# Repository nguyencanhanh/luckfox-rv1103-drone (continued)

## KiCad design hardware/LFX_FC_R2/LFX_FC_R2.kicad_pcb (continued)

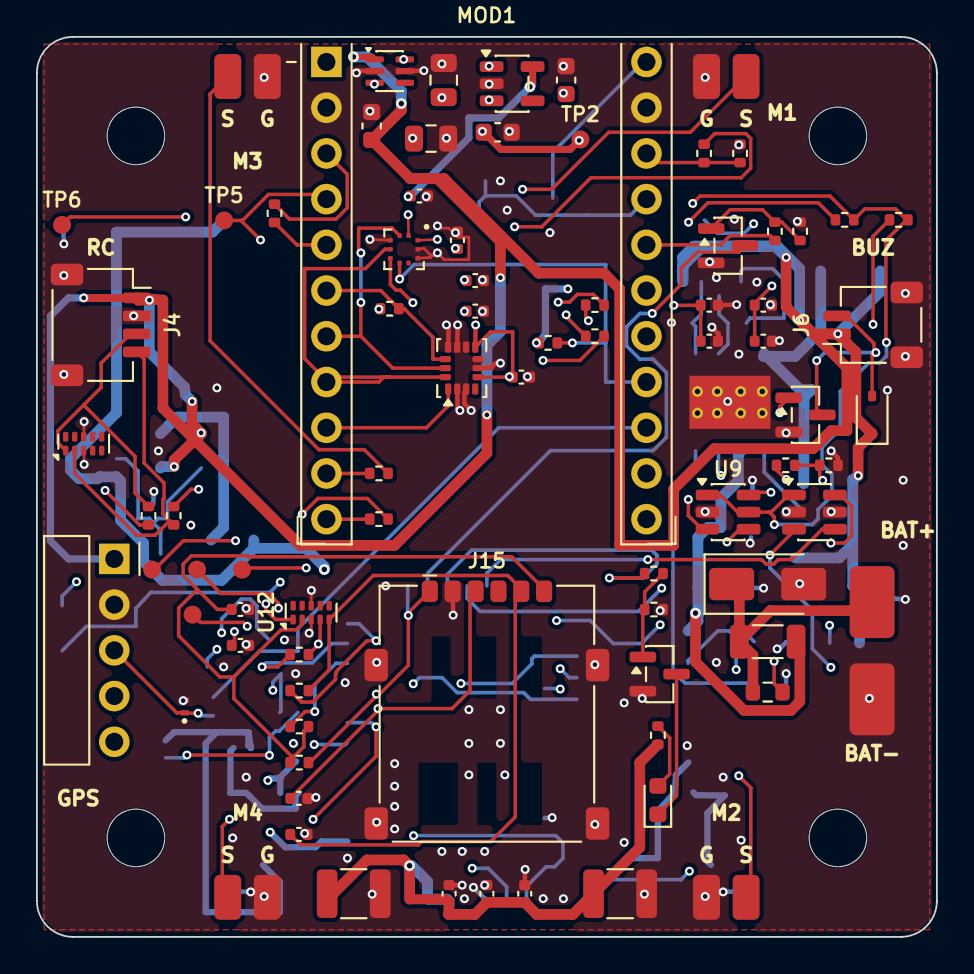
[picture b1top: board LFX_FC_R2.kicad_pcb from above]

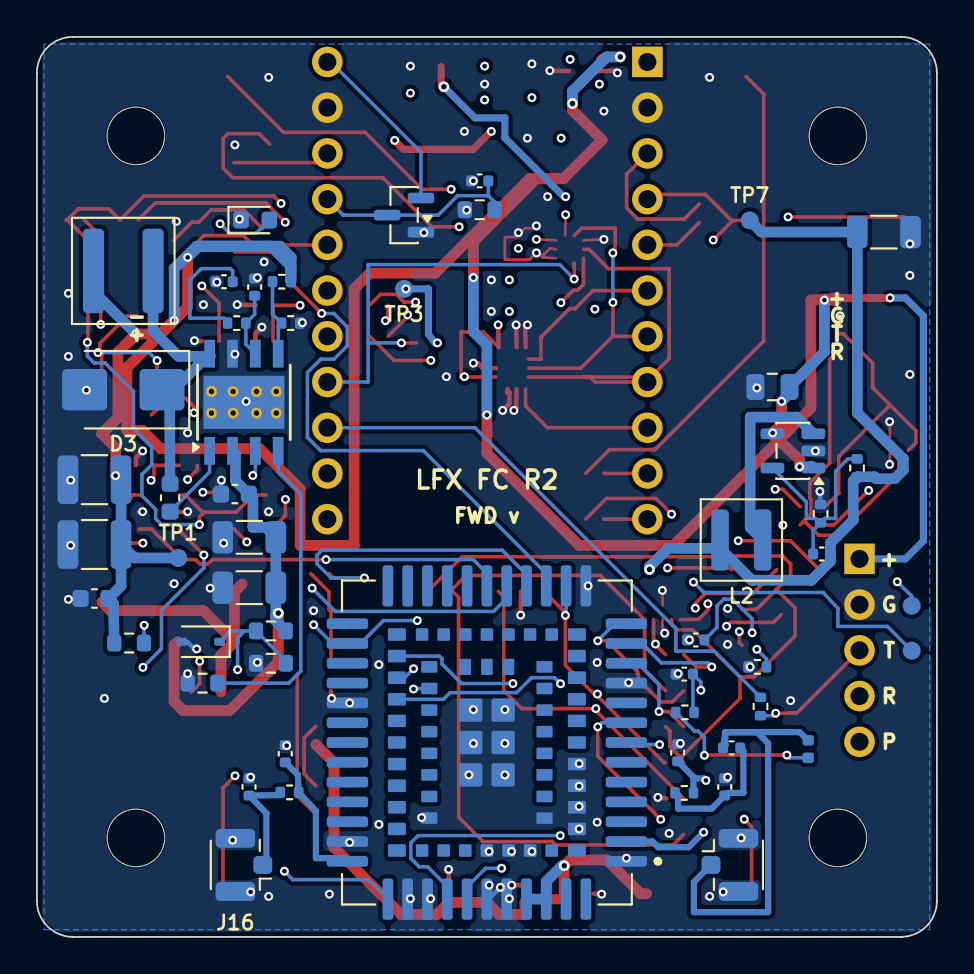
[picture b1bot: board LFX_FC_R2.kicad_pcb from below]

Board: 4 copper layers, 50.0 x 50.0 mm, 142 parts (52 on the bottom side), 76 nets.

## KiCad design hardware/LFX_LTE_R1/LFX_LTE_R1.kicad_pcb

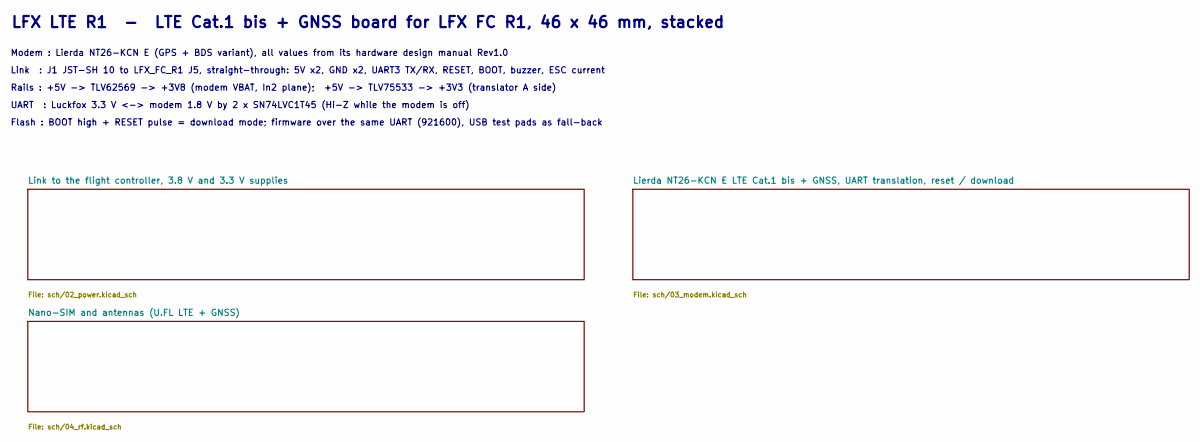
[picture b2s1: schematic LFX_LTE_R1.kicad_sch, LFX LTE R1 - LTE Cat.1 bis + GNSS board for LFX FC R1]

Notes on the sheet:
LFX LTE R1 - LTE Cat.1 bis + GNSS board for LFX FC R1, 46 x 46 mm, stacked
Modem : Lierda NT26-KCN E (GPS + BDS variant), all values from its hardware design manual Rev1.0
Link : J1 JST-SH 10 to LFX_FC_R1 J5, straight-through: 5V x2, GND x2, UART3 TX/RX, RESET, BOOT, buzzer, ESC current
Rails : +5V -> TLV62569 -> +3V8 (modem VBAT, In2 plane); +5V -> TLV75533 -> +3V3 (translator A side)
UART : Luckfox 3.3 V <-> modem 1.8 V by 2 x SN74LVC1T45 (Hi-Z while the modem is off)
Flash : BOOT high + RESET pulse = download mode; firmware over the same UART (921600), USB test pads as fall-back

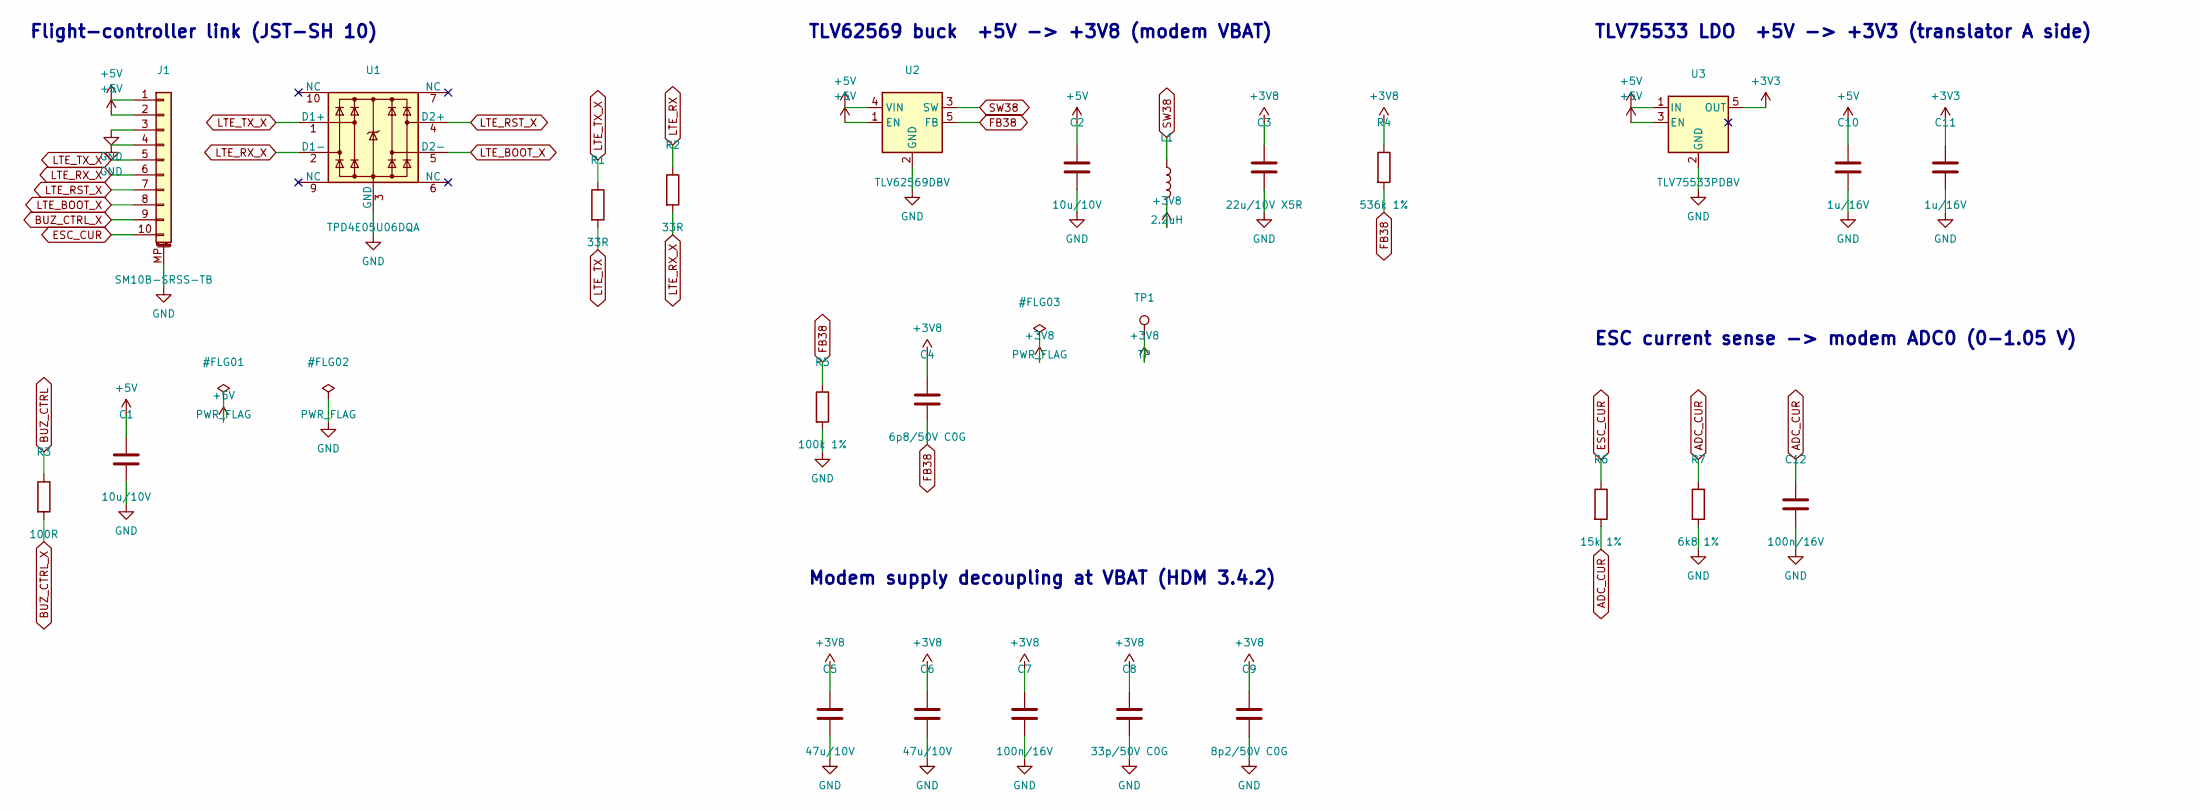
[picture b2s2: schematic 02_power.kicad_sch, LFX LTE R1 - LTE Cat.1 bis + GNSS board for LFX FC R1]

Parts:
C1, C2: 10u/10V; C_0805_2012Metric
C3: 22u/10V X5R; C_1206_3216Metric
C4: 6p8/50V C0G; C_0402_1005Metric
C5, C6: 47u/10V; C_1210_3225Metric
C7, C12: 100n/16V; C_0402_1005Metric
C8: 33p/50V C0G; C_0402_1005Metric
C9: 8p2/50V C0G; C_0402_1005Metric
C10, C11: 1u/16V; C_0603_1608Metric
J1: SM10B-SRSS-TB; JST_SH_SM10B-SRSS-TB_1x10-1MP_P1.00mm_Horizontal
L1: 2.2uH; L_Coilcraft_XAL4020-XXX
R1, R2: 33R; R_0402_1005Metric
R3: 100R; R_0402_1005Metric
R4: 536k 1%; R_0402_1005Metric
R5: 100k 1%; R_0402_1005Metric
R6: 15k 1%; R_0603_1608Metric
R7: 6k8 1%; R_0603_1608Metric
TP1: TP; TestPad_1.0mm
U1: TPD4E05U06DQA; USON-10_2.5x1.0mm_P0.5mm
U2: TLV62569DBV; SOT-23-5
U3: TLV75533PDBV; SOT-23-5

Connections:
+3V3: C11.1, U3.5 (OUT); also elsewhere on the board
+3V8: C3.1, C4.1, C5.1, C6.1, C7.1, C8.1, C9.1, L1.2, R4.1, TP1.1; also elsewhere on the board
+5V: C1.1, C2.1, C10.1, J1.1, J1.2, U2.1 (EN), U2.4 (VIN), U3.1 (IN), U3.3 (EN)
ADC_CUR: C12.1, R6.2, R7.1; also elsewhere on the board
BUZ_CTRL: R3.1; also elsewhere on the board
BUZ_CTRL_X: J1.9, R3.2
ESC_CUR: J1.10, R6.1
FB38: C4.2, R4.2, R5.1, U2.5 (FB)
GND: C1.2, C2.2, C3.2, C5.2, C6.2, C7.2, C8.2, C9.2, C10.2, C11.2, C12.2, J1.3, J1.4, J1.MP (MountPin), R5.2, R7.2, U1.3 (GND), U1.8 (GND), U2.2 (GND), U3.2 (GND); also elsewhere on the board
LTE_BOOT_X: J1.8, U1.5 (D2-); also elsewhere on the board
LTE_RST_X: J1.7, U1.4 (D2+); also elsewhere on the board
LTE_RX: R2.1; also elsewhere on the board
LTE_RX_X: J1.6, R2.2, U1.2 (D1-)
LTE_TX: R1.2; also elsewhere on the board
LTE_TX_X: J1.5, R1.1, U1.1 (D1+)
SW38: L1.1, U2.3 (SW)

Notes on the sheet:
Flight-controller link (JST-SH 10)
TLV62569 buck +5V -> +3V8 (modem VBAT)
Modem supply decoupling at VBAT (HDM 3.4.2)
TLV75533 LDO +5V -> +3V3 (translator A side)
ESC current sense -> modem ADC0 (0-1.05 V)

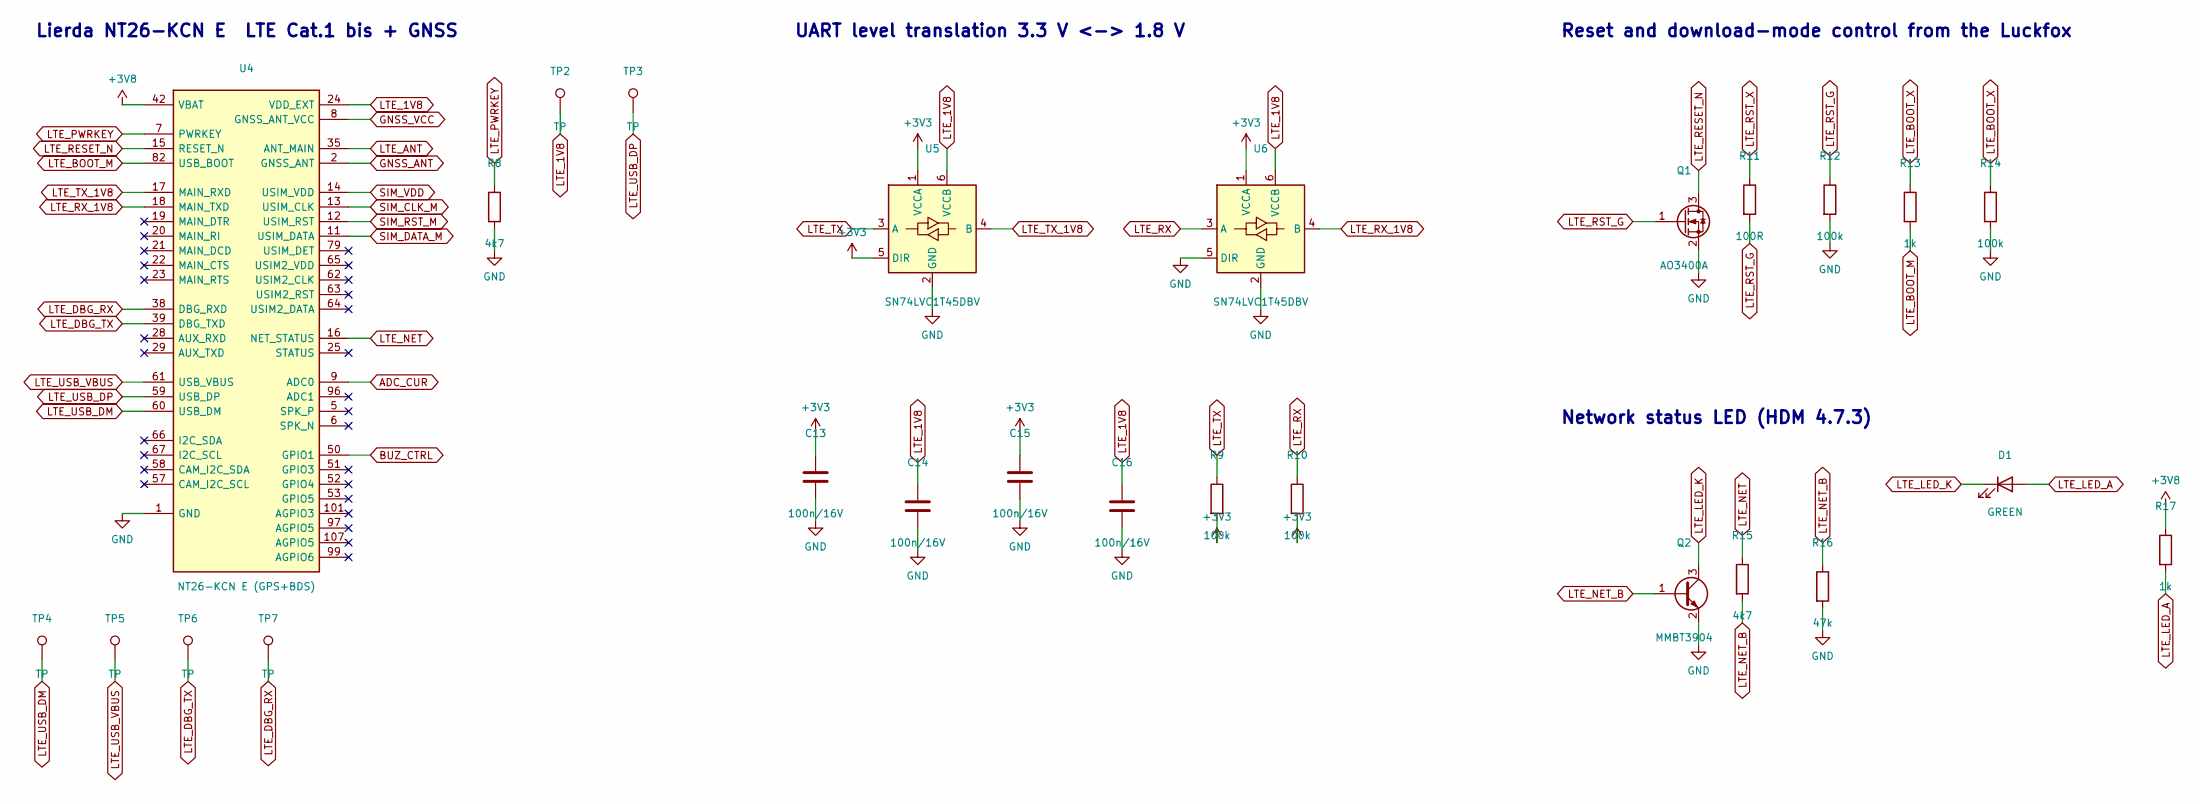
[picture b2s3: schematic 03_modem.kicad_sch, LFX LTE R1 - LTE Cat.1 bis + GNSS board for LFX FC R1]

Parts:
C13, C14, C15, C16: 100n/16V; C_0402_1005Metric
D1: GREEN; LED_0603_1608Metric
Q1: AO3400A; SOT-23
Q2: MMBT3904; SOT-23
R8, R15: 4k7; R_0402_1005Metric
R9, R10, R12, R14: 100k; R_0402_1005Metric
R11: 100R; R_0402_1005Metric
R13, R17: 1k; R_0402_1005Metric
R16: 47k; R_0402_1005Metric
TP2, TP3, TP4, TP5, TP6, TP7: TP; TestPad_1.0mm
U4: NT26-KCN E (GPS+BDS); Lierda_NT26-KCN_LCC-LGA-109_15.8x17.7mm
U5, U6: SN74LVC1T45DBV; SOT-23-6

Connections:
+3V3: C13.1, C15.1, R9.2, R10.2, U5.1 (VCCA), U5.5 (DIR), U6.1 (VCCA); also elsewhere on the board
+3V8: R17.1, U4.42 (VBAT), U4.43 (VBAT); also elsewhere on the board
ADC_CUR: U4.9 (ADC0); also elsewhere on the board
BUZ_CTRL: U4.50 (GPIO1); also elsewhere on the board
GND: C13.2, C14.2, C15.2, C16.2, Q1.2 (S), Q2.2 (E), R8.2, R12.2, R14.2, R16.2, U4.1 (GND), U4.10 (GND), U4.27 (GND), U4.34 (GND), U4.36 (GND), U4.37 (GND), U4.40 (GND), U4.41 (GND), U4.45 (GND), U4.46 (GND), U4.47 (GND), U4.48 (GND), U4.70 (GND), U4.71 (GND), U4.72 (GND), U4.73 (GND), U4.88 (GND), U4.89 (GND), U4.90 (GND), U4.91 (GND), U4.92 (GND), U4.93 (GND), U4.94 (GND), U4.95 (GND), U5.2 (GND), U6.2 (GND), U6.5 (DIR); also elsewhere on the board
GNSS_ANT: U4.2 (GNSS_ANT); also elsewhere on the board
GNSS_VCC: U4.8 (GNSS_ANT_VCC); also elsewhere on the board
LTE_1V8: C14.1, C16.1, TP2.1, U4.24 (VDD_EXT), U5.6 (VCCB), U6.6 (VCCB)
LTE_ANT: U4.35 (ANT_MAIN); also elsewhere on the board
LTE_BOOT_M: R13.2, U4.82 (USB_BOOT)
LTE_BOOT_X: R13.1, R14.1; also elsewhere on the board
LTE_DBG_RX: TP7.1, U4.38 (DBG_RXD)
LTE_DBG_TX: TP6.1, U4.39 (DBG_TXD)
LTE_LED_A: D1.2 (A), R17.2
LTE_LED_K: D1.1 (K), Q2.3 (C)
LTE_NET: R15.1, U4.16 (NET_STATUS)
LTE_NET_B: Q2.1 (B), R15.2, R16.1
LTE_PWRKEY: R8.1, U4.7 (PWRKEY)
LTE_RESET_N: Q1.3 (D), U4.15 (RESET_N)
LTE_RST_G: Q1.1 (G), R11.2, R12.1
LTE_RST_X: R11.1; also elsewhere on the board
LTE_RX: R10.1, U6.3 (A); also elsewhere on the board
LTE_RX_1V8: U4.18 (MAIN_TXD), U6.4 (B)
LTE_TX: R9.1, U5.3 (A); also elsewhere on the board
LTE_TX_1V8: U4.17 (MAIN_RXD), U5.4 (B)
LTE_USB_DM: TP4.1, U4.60 (USB_DM)
LTE_USB_DP: TP3.1, U4.59 (USB_DP)
LTE_USB_VBUS: TP5.1, U4.61 (USB_VBUS)
SIM_CLK_M: U4.13 (USIM_CLK); also elsewhere on the board
SIM_DATA_M: U4.11 (USIM_DATA); also elsewhere on the board
SIM_RST_M: U4.12 (USIM_RST); also elsewhere on the board
SIM_VDD: U4.14 (USIM_VDD); also elsewhere on the board

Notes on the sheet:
Lierda NT26-KCN E LTE Cat.1 bis + GNSS
UART level translation 3.3 V <-> 1.8 V
Reset and download-mode control from the Luckfox
Network status LED (HDM 4.7.3)

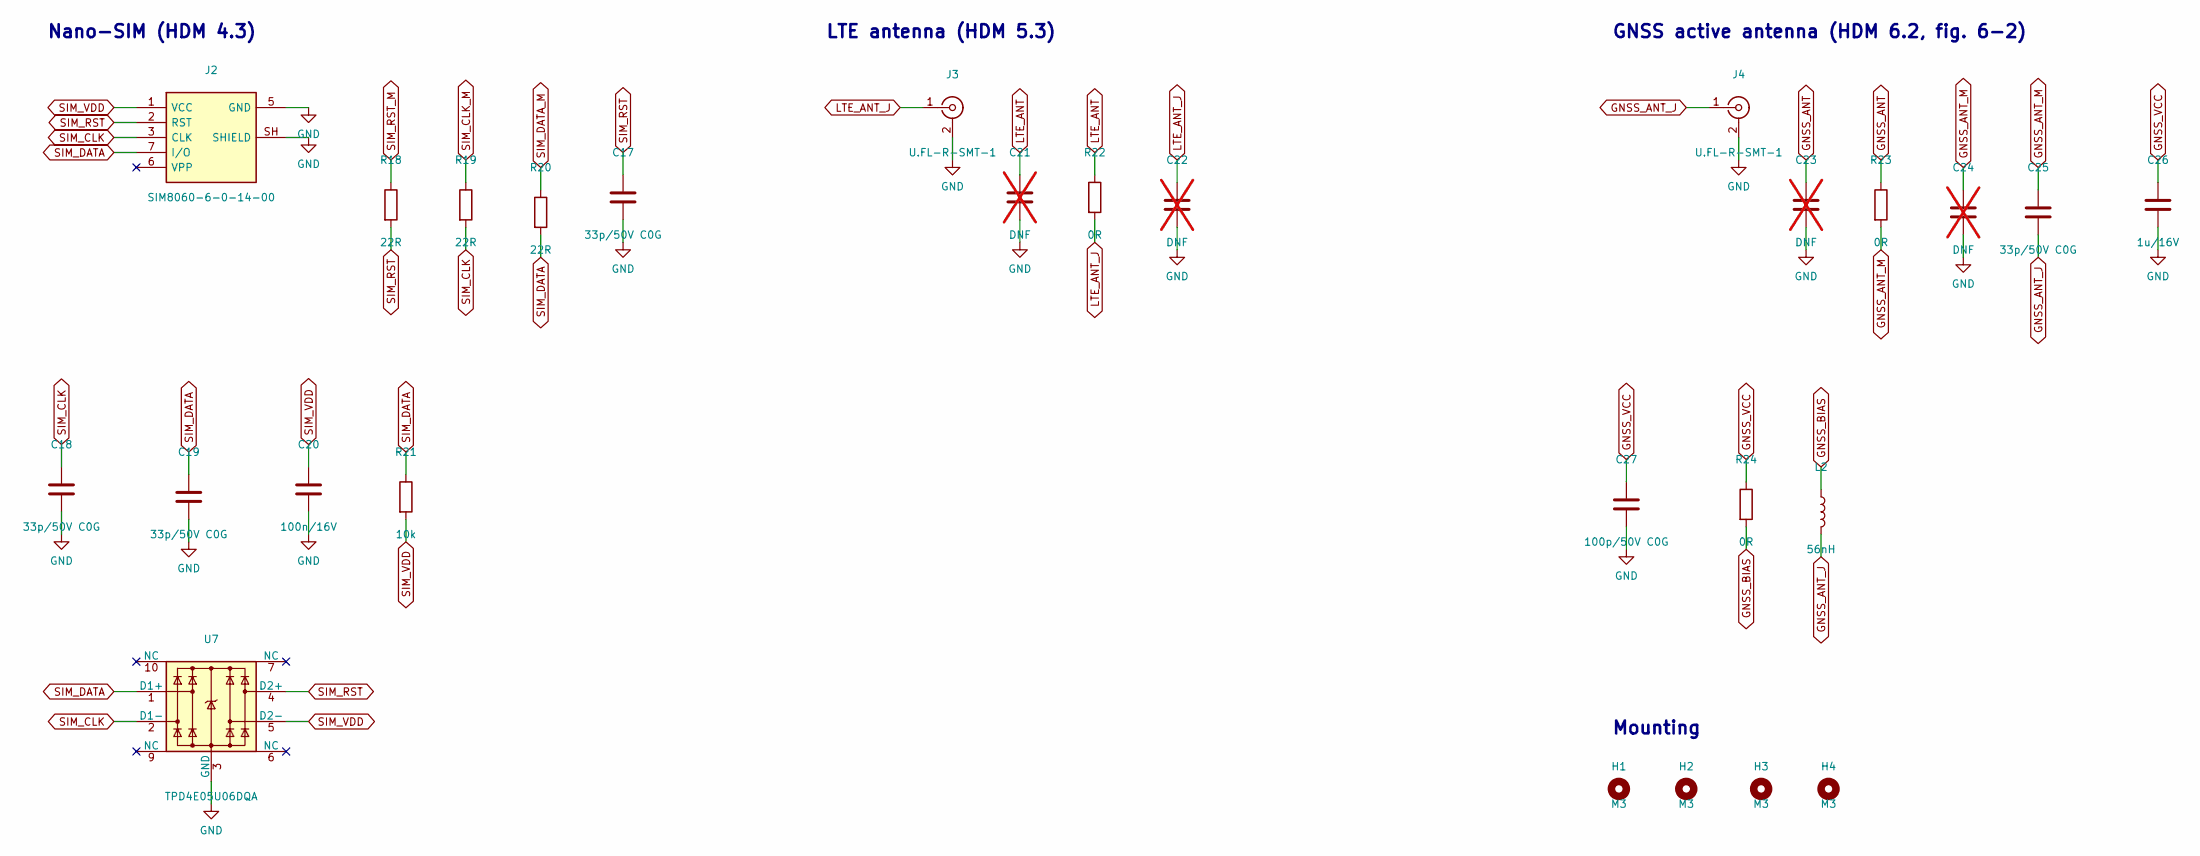
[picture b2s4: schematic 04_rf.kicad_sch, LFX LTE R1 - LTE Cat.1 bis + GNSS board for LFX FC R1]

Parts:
C17, C18, C19, C25: 33p/50V C0G; C_0402_1005Metric
C20: 100n/16V; C_0402_1005Metric
C21, C22, C23, C24: DNF; C_0402_1005Metric; not fitted
C26: 1u/16V; C_0402_1005Metric
C27: 100p/50V C0G; C_0402_1005Metric
H1, H2, H3, H4: M3; MountingHole_3.2mm_M3
J2: SIM8060-6-0-14-00; nanoSIM_GCT_SIM8060-6-0-14-00
J3, J4: U.FL-R-SMT-1; U.FL_Hirose_U.FL-R-SMT-1_Vertical
L2: 56nH; L_0402_1005Metric
R18, R19, R20: 22R; R_0402_1005Metric
R21: 10k; R_0402_1005Metric
R22, R23, R24: 0R; R_0402_1005Metric
U7: TPD4E05U06DQA; USON-10_2.5x1.0mm_P0.5mm

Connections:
GND: C17.2, C18.2, C19.2, C20.2, C21.2, C22.2, C23.2, C24.2, C26.2, C27.2, J2.5 (GND), J2.SH (SHIELD), J3.2 (Ext), J4.2 (Ext), U7.3 (GND), U7.8 (GND); also elsewhere on the board
GNSS_ANT: C23.1, R23.1; also elsewhere on the board
GNSS_ANT_J: C25.2, J4.1 (In), L2.2
GNSS_ANT_M: C24.1, C25.1, R23.2
GNSS_BIAS: L2.1, R24.2
GNSS_VCC: C26.1, C27.1, R24.1; also elsewhere on the board
LTE_ANT: C21.1, R22.1; also elsewhere on the board
LTE_ANT_J: C22.1, J3.1 (In), R22.2
SIM_CLK: C18.1, J2.3 (CLK), R19.2, U7.2 (D1-)
SIM_CLK_M: R19.1; also elsewhere on the board
SIM_DATA: C19.1, J2.7 (I/O), R20.2, R21.1, U7.1 (D1+)
SIM_DATA_M: R20.1; also elsewhere on the board
SIM_RST: C17.1, J2.2 (RST), R18.2, U7.4 (D2+)
SIM_RST_M: R18.1; also elsewhere on the board
SIM_VDD: C20.1, J2.1 (VCC), R21.2, U7.5 (D2-); also elsewhere on the board

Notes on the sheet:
Nano-SIM (HDM 4.3)
LTE antenna (HDM 5.3)
GNSS active antenna (HDM 6.2, fig. 6-2)
Mounting

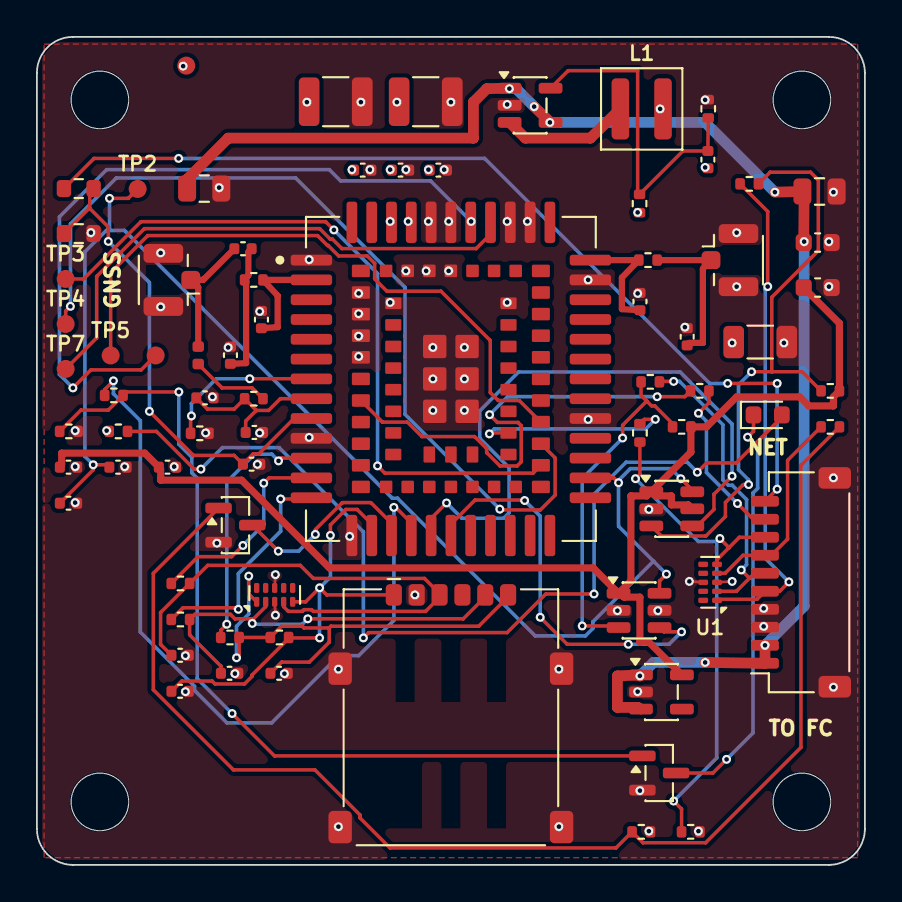
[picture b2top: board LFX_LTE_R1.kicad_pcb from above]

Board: 4 copper layers, 46.0 x 46.0 mm, 78 parts (0 on the bottom side), 46 nets.
